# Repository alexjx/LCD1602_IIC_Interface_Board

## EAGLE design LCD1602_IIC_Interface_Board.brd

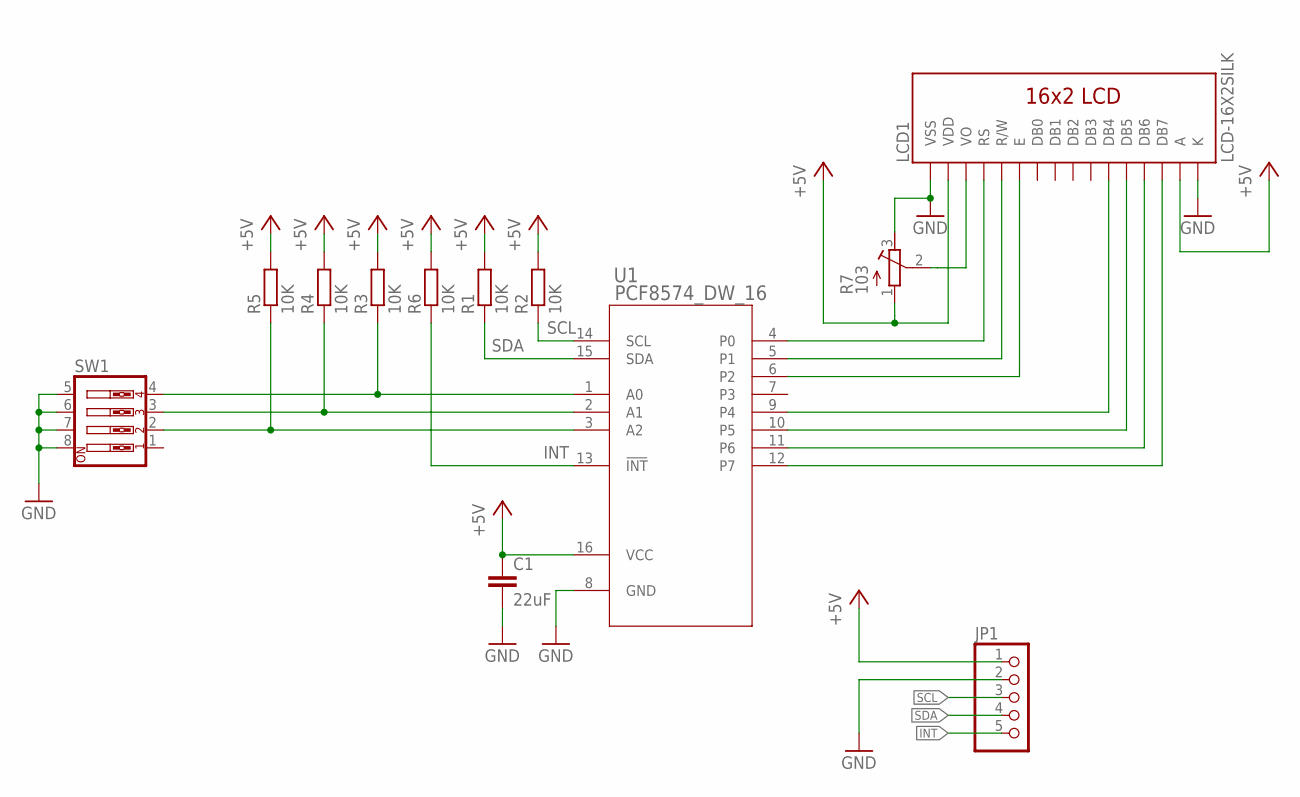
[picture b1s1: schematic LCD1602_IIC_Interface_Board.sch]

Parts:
C1: 22uF; C1206
JP1: PINHD-1X5; 1X05
LCD1: LCD-16X2SILK; LCD-16X2
R1, R2, R3, R4, R5, R6: 10K; R0603
R7: 103; RTRIM3296W
SW1: SW_DIP-4; EDG-04
U1: PCF8574_DW_16; DW16

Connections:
+5V: C1.1, JP1.1, LCD1.2 (VDD), LCD1.15 (A), R1.2, R2.2, R3.2, R4.2, R5.2, R6.2, R7.1 (A), U1.16 (VCC)
GND: C1.2, JP1.2, LCD1.1 (VSS), LCD1.16 (K), R7.3 (E), SW1.5, SW1.6, SW1.7, SW1.8, U1.8 (GND)
INT: JP1.5, R6.1, U1.13 (!INT)
unnamed: LCD1.4 (RS), U1.4 (P0)
unnamed: LCD1.5 (R/W), U1.5 (P1)
unnamed: LCD1.11 (DB4), U1.9 (P4)
unnamed: LCD1.12 (DB5), U1.10 (P5)
unnamed: LCD1.13 (DB6), U1.11 (P6)
unnamed: LCD1.14 (DB7), U1.12 (P7)
unnamed: LCD1.6 (E), U1.6 (P2)
unnamed: R3.1, SW1.4, U1.1 (A0)
unnamed: R4.1, SW1.3, U1.2 (A1)
unnamed: R5.1, SW1.2, U1.3 (A2)
unnamed: LCD1.3 (VO), R7.2 (S)
SCL: JP1.3, R2.1, U1.14 (SCL)
SDA: JP1.4, R1.1, U1.15 (SDA)

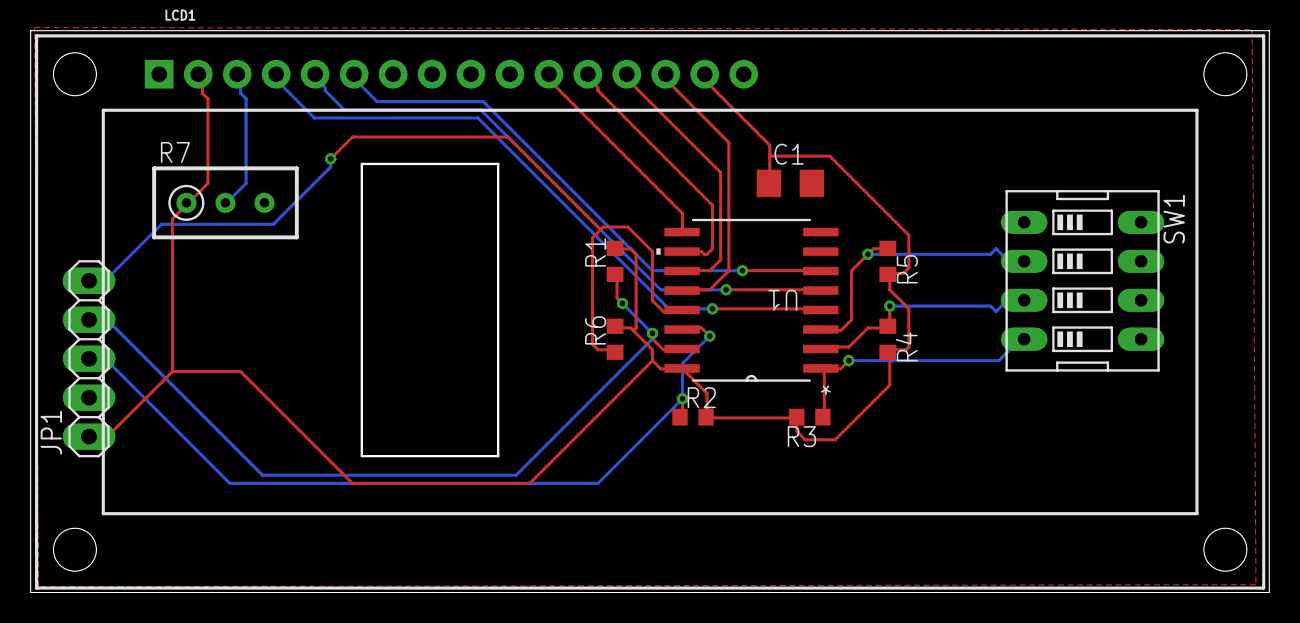
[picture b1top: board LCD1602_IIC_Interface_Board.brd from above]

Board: 2 copper layers, 80.6 x 36.5 mm, 12 parts (0 on the bottom side), 16 nets.

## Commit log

2017-09-06 Rename the gerber files

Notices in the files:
parts and their libraries:
SparkFun-Displays: Licensing: Creative Commons ShareAlike 4.0 International - https://creativecommons.org/licenses/by-sa/4.0
